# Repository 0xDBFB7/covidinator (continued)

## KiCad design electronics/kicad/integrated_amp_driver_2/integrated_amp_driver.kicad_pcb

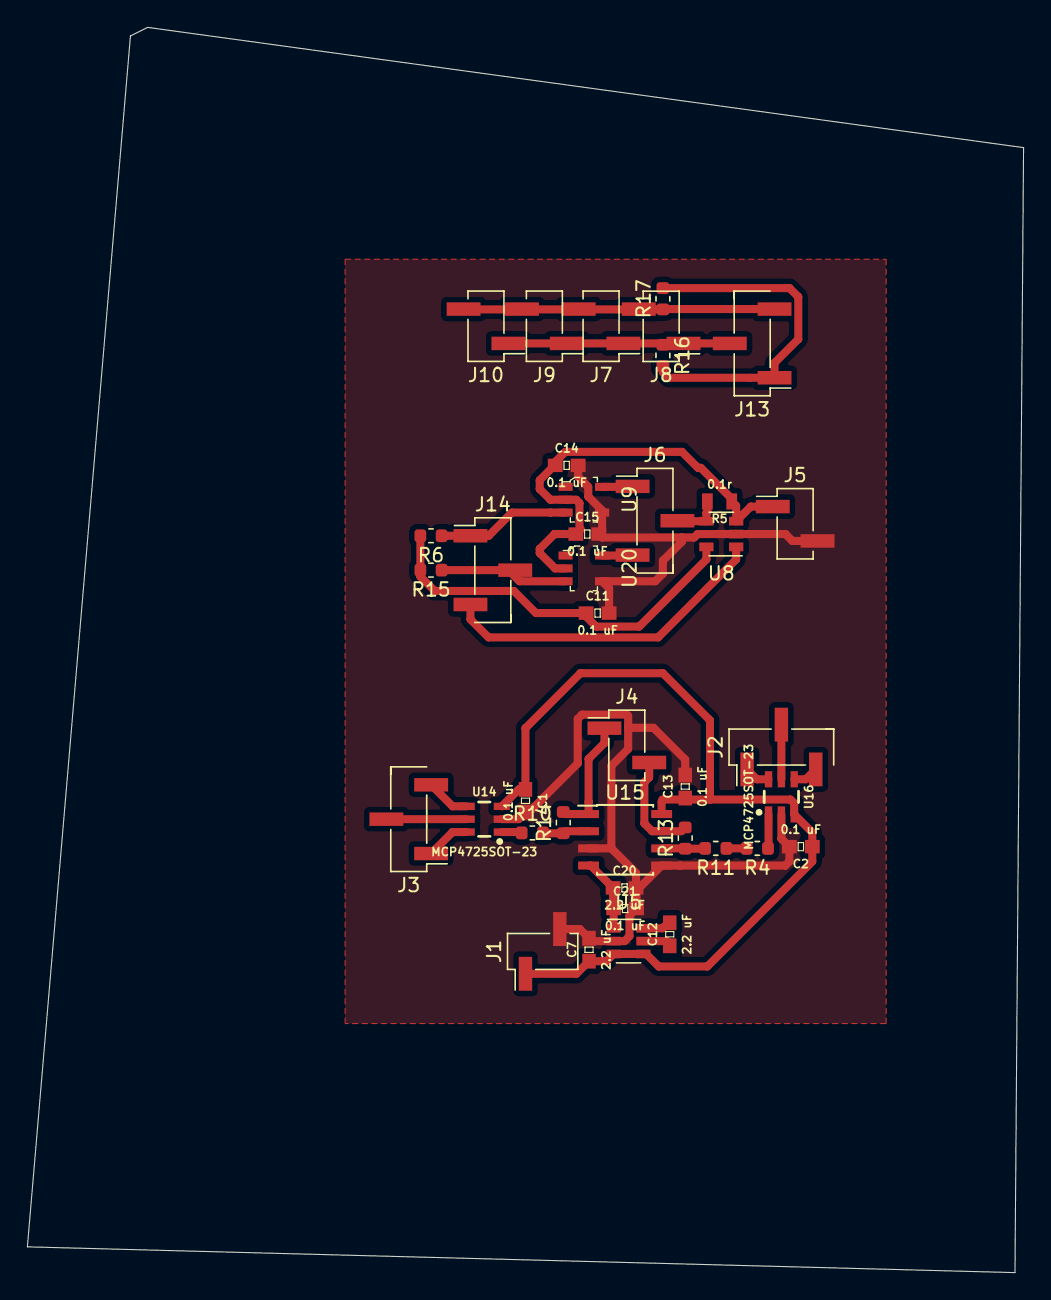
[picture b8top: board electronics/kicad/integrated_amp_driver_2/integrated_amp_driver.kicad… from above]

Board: 2 copper layers, 73.7 x 92.1 mm, 39 parts (0 on the bottom side), 23 nets.

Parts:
C1, C2, C11, C13, C14, C15, C21: 0.1 uF; 0603
C7, C12, C20: 2.2 uF; 0603
J1, J4, J5, J7, J8, J9, J10: CONN_02; PinHeader_1x02_P2.54mm_Vertical_SMD_Pin1Left
J2, J3, J6, J13, J14: CONN_02; PinHeader_1x03_P2.54mm_Vertical_SMD_Pin1Left
R4, R6, R10, R11, R13, R14, R15: 1k; R_0603_1608Metric
R5: 0.1r; 0805
R16, R17: 4.7k; R_0603_1608Metric
U5: LM2776; SOT-23-6
U8: INA194; SOT-23-5
U9, U20: MCP1416T-E_OT; SOT-753
U14, U16: MCP4725SOT-23; SOT23-6
U15: TS912IDT; SOIC-8_3.9x4.9mm_P1.27mm

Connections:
3.3V: C11.1, J13.1, R6.2, R15.2, R16.2, R17.2, U8.5
5V: C1.1, C2.1, C7.1, C13.1, C14.1, C15.1, J1.1, J5.1, R5.1, U5.3, U5.4, U8.3, U9.2, U14.3, U15.8, U16.3, U20.2
-5V: C20.1, C21.1, U5.1, U15.4
AMP_DRAIN_CONTROL_: J6.3, U20.5
AMP_DRAIN_SUPPLY: J6.2, R5.2, U8.4
AMP_GAIN_CONTROL_: J4.1, R14.2, U15.1
AMP_GATE_CONTROL_: J4.2, R13.2, U15.7
GAIN_DAC_I2C_SELECT: J3.1, U14.6
GATE_DAC_I2C_SELECT: J2.1, U16.6
GND: C1.2, C2.2, C7.2, C11.2, C13.2, C14.2, C15.2, C20.2, C21.2, J1.2, J5.2, U5.2, U8.2, U9.4, U14.2, U15.3, U15.5, U16.2, U20.4
unnamed: C12.1, U5.5
unnamed: C12.2, U5.6
unnamed: R4.1, U16.1
unnamed: R10.1, U14.1
unnamed: R10.2, R14.1, U15.2
unnamed: R4.2, R11.1
unnamed: R11.2, R13.1, U15.6
SCL: J2.2, J3.2, J7.1, J8.1, J9.1, J10.1, J13.2, R16.1, U14.5, U16.5
SDA: J2.3, J3.3, J7.2, J8.2, J9.2, J10.2, J13.3, R17.1, U14.4, U16.4
VCO_POWER_CONTROL_: J6.1, U9.5
current_sense_output: J14.3, U8.1
~AMP_DRAIN_CONTROL: J14.2, R15.1, U20.3
~VCO_POWER_CONTROL: J14.1, R6.1, U9.3
